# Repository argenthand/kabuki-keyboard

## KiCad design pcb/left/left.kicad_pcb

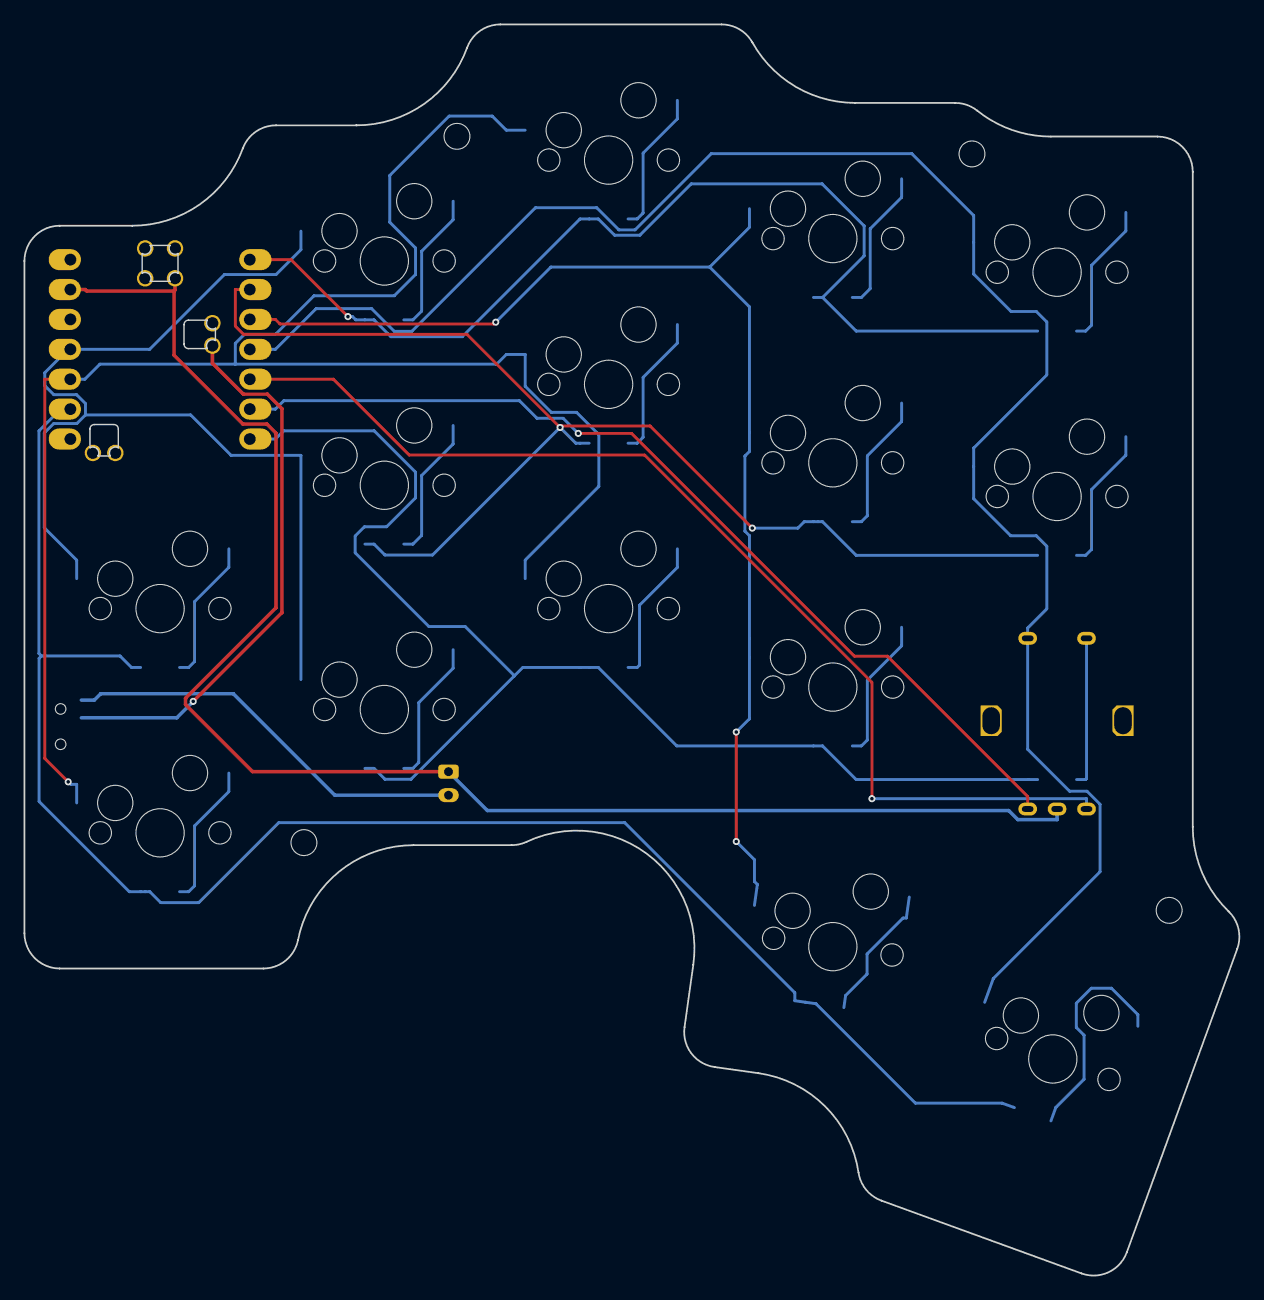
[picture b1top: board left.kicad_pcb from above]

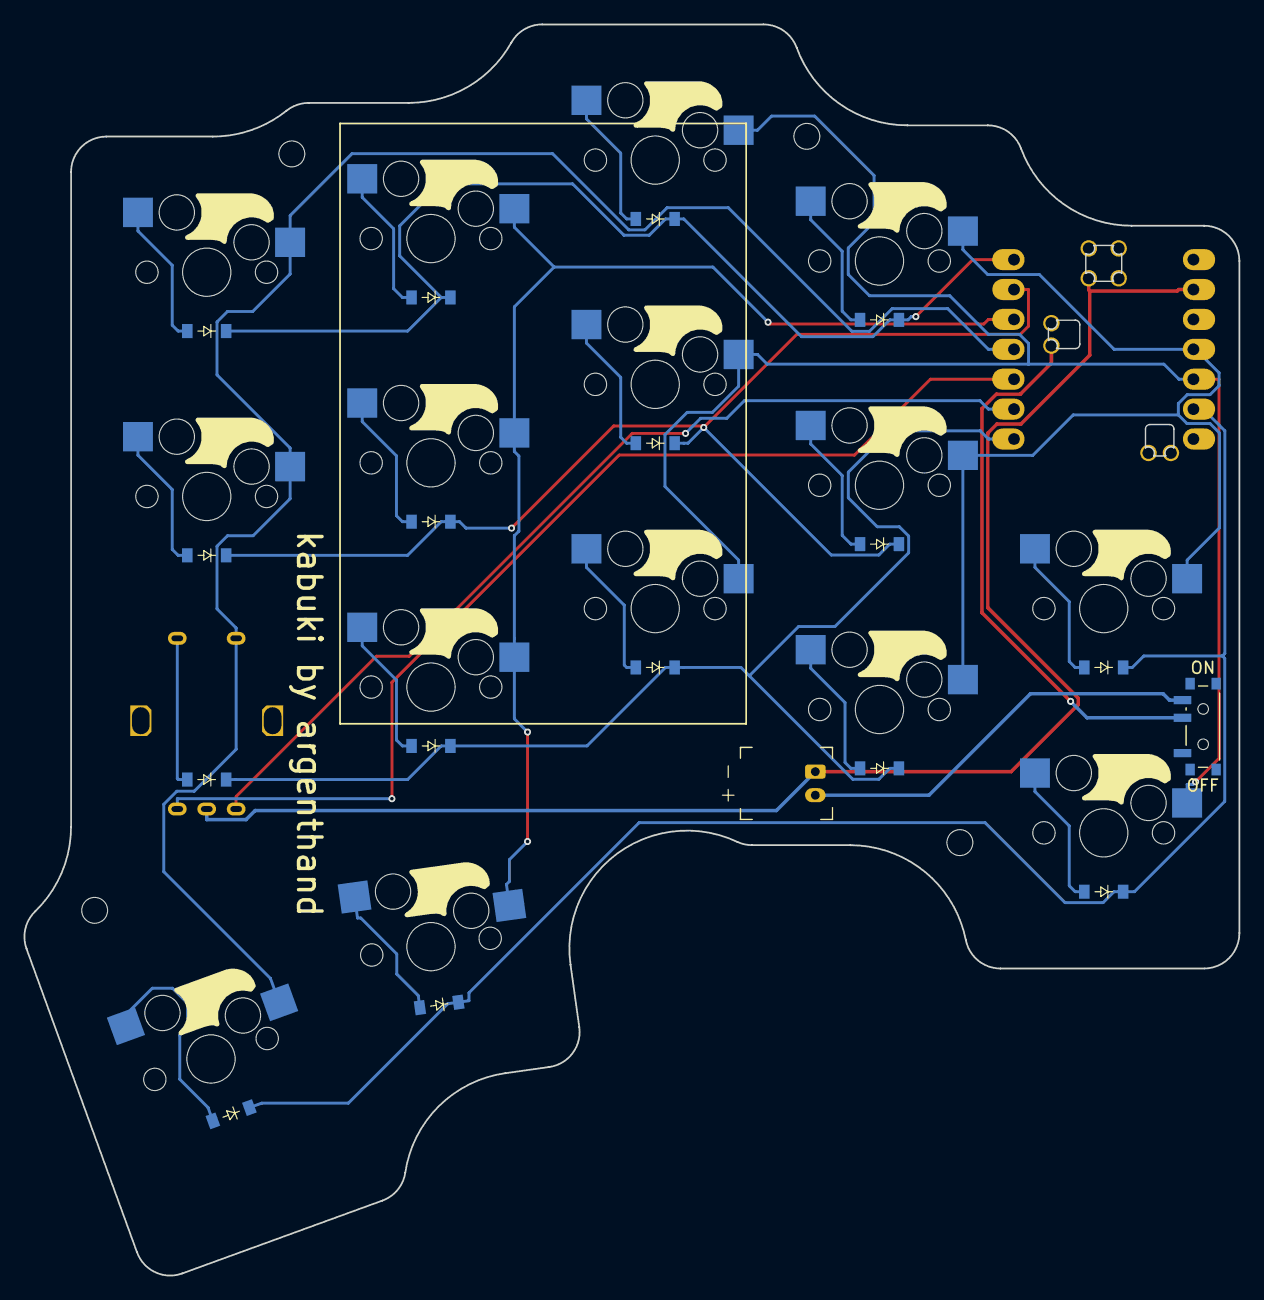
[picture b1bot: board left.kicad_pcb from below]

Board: 2 copper layers, 103.2 x 106.3 mm, 39 parts (34 on the bottom side), 29 nets.

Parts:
D1, D2, D3, D4, D5, D6, D7, D8, D9, D10, D11, D12, D13, D14, D15, D16: diode_tht_sod123
JST1: battery_connector_jst_ph_2
MCU1: XIAO-BLE
MH1, MH2, MH3, MH4: mounting_hole_npth
PWR1: power_switch_smd_side
RE1: rotary_encoder_ec11_ec12
S1, S2, S3, S4, S5, S6, S7, S8, S9, S10, S11, S12, S13, S14, S15: switch_mx

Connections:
BAT_P: JST1.2, PWR1.3
BAT_SW: MCU1.19, PWR1.2
C0: MCU1.11, S2.1, S3.1, S4.1, S5.1
C1: MCU1.10, S1.1, S6.1, S7.1, S8.1
C2: MCU1.3, S9.1, S10.1, S11.1, S14.1
C3: MCU1.4, RE1.S1, S12.1, S13.1, S15.1
ENC_A: MCU1.5, RE1.A
ENC_B: MCU1.6, RE1.C
GND: JST1.1, MCU1.13, MCU1.17, RE1.B
R0: D5.1, D8.1, D11.1, D14.1, MCU1.1
R1: D4.1, D7.1, D10.1, D13.1, MCU1.2
R2: D3.1, D6.1, D9.1, D12.1, MCU1.7
R3: D1.1, D2.1, D15.1, D16.1, MCU1.9
far_thumb: D16.2, S15.2
index_bottom: D9.2, S9.2
index_home: D10.2, S10.2
index_top: D11.2, S11.2
inner_bottom: D12.2, RE1.S2
inner_home: D13.2, S12.2
inner_top: D14.2, S13.2
middle_bottom: D6.2, S6.2
middle_home: D7.2, S7.2
middle_top: D8.2, S8.2
near_thumb: D15.2, S14.2
pinky_bottom: D1.2, S1.2
pinky_home: D2.2, S2.2
ring_bottom: D3.2, S3.2
ring_home: D4.2, S4.2
ring_top: D5.2, S5.2
